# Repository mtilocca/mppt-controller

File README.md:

# MPPT solar charge controller (STM32H743, LM5177 buck-boost)

PV 0-48 V, battery 12-48 V, switched load, DC feed + control port for an external 220 V inverter, Ethernet / isolated CAN / isolated RS485 / USB-C / display.
Design only (not built, not validated). KiCad 10 project generated from code.

PCB editor (routed copper, 195 x 128 mm, 4 layers) and the 3D viewer:

| Doc | Content |
|---|---|
| [docs/00-overview.md](docs/00-overview.md) | What it is, pictures (schematic, PCB, 3D), use cases, comparison with a standard MPPT controller |
| [docs/01-requirements.md](docs/01-requirements.md) | Requirements and assumptions |
| [docs/02-architecture.md](docs/02-architecture.md) | Architecture, part choices, open design items |
| [docs/03-pinmap.md](docs/03-pinmap.md) | STM32 pin allocation (generated) |
| [docs/04-handover.md](docs/04-handover.md) | Current state, what is left, pipeline commands |

Sources: `hardware/mppt_controller.py` (SKiDL generator) -> schematic -> `hardware/place_pcb.py`, routing scripts, `hardware/rebuild.sh`.

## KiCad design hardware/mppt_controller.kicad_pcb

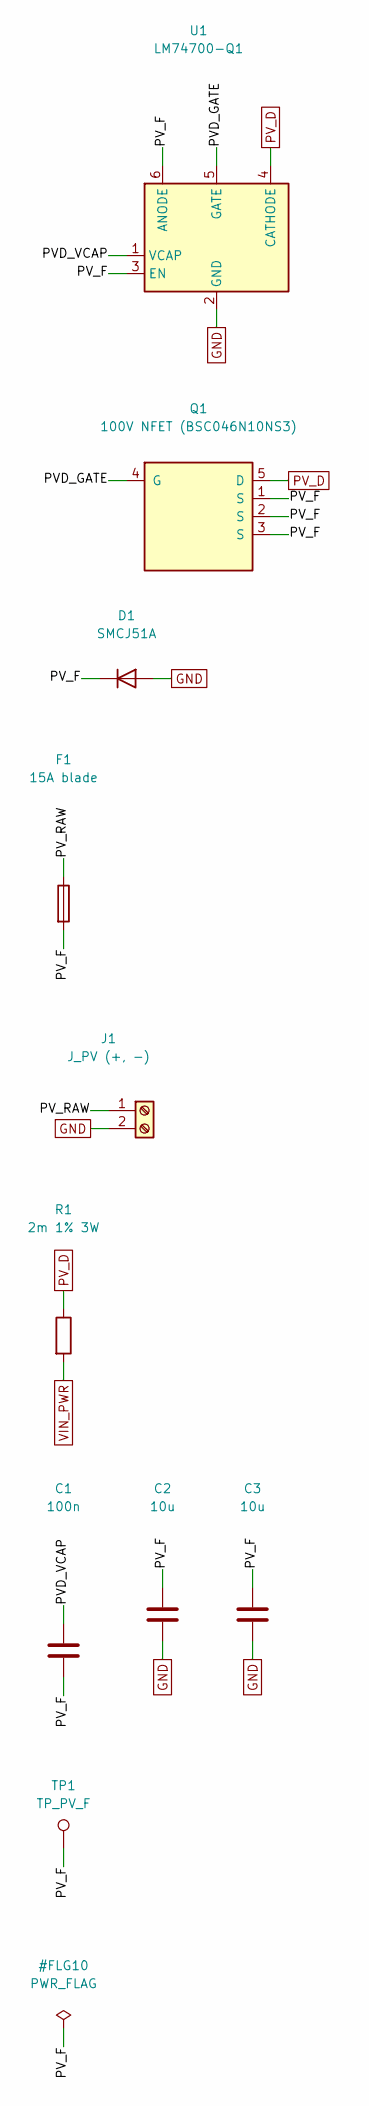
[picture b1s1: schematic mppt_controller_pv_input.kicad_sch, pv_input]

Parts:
C1: 100n; C_0805_2012Metric
C2, C3: 10u; C_1210_3225Metric
D1: SMCJ51A; D_SMC
F1: 15A blade; Fuseholder_Blade_Mini_Keystone_3568
J1: J_PV (+, -); TerminalBlock_Phoenix_MKDS-3-2-5.08_1x02_P5.08mm_Horizontal
Q1: 100V NFET (BSC046N10NS3); TDSON-8-1
R1: 2m 1% 3W; R_2512_6332Metric
TP1: TP_PV_F; TestPoint_Pad_D1.5mm
U1: LM74700-Q1; SOT-23-6

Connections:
/pv_input/PVD_GATE: Q1.4 (G), U1.5 (GATE)
/pv_input/PVD_VCAP: C1.1, U1.1 (VCAP)
/pv_input/PV_F: C1.2, C2.1, C3.1, D1.1 (K), F1.2, Q1.1 (S), Q1.2 (S), Q1.3 (S), TP1.1, U1.3 (EN), U1.6 (ANODE)
/pv_input/PV_RAW: F1.1, J1.1
GND: C2.2, C3.2, D1.2 (A), J1.2, U1.2 (GND); also elsewhere on the board
PV_D: Q1.5 (D), R1.1, U1.4 (CATHODE); also elsewhere on the board
VIN_PWR: R1.2; also elsewhere on the board

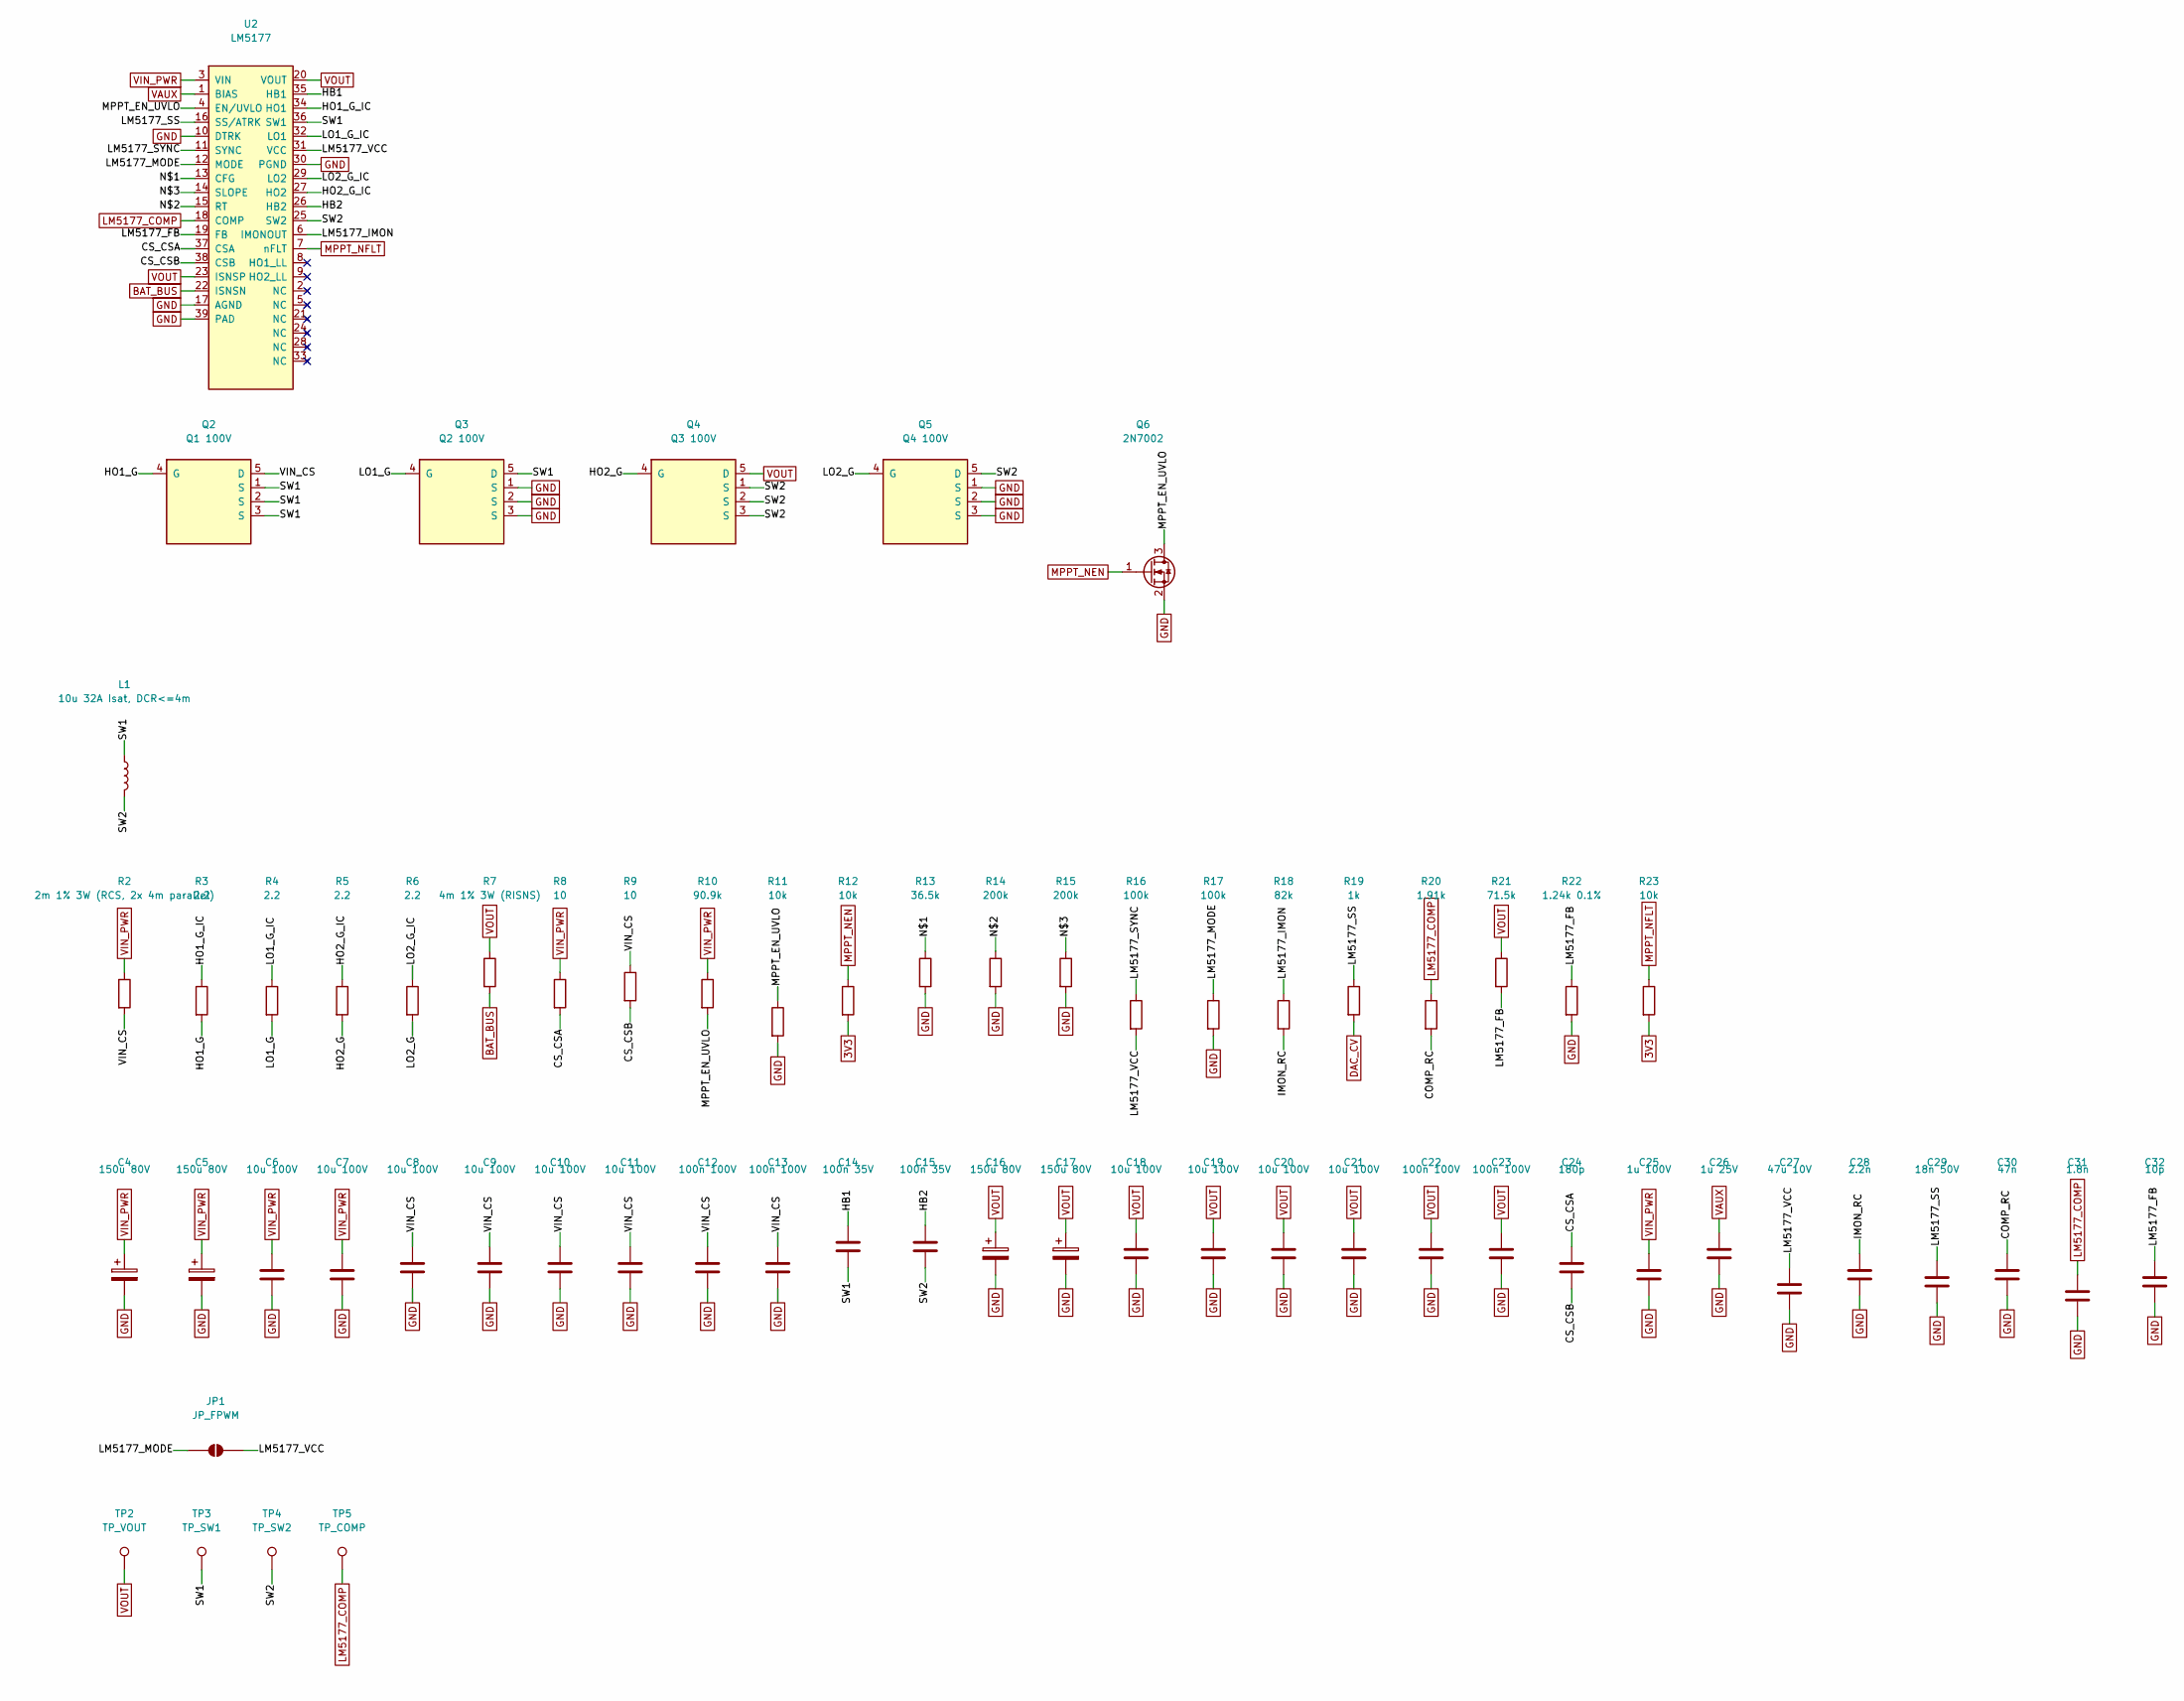
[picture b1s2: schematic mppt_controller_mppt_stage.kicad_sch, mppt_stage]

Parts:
C4, C5, C16, C17: 150u 80V; CP_Elec_10x10.5
C6, C7, C8, C9, C10, C11, C18, C19, C20, C21: 10u 100V; C_1210_3225Metric
C12, C13, C22, C23: 100n 100V; C_0805_2012Metric
C14, C15: 100n 35V; C_0603_1608Metric
C24: 180p; C_0603_1608Metric
C25: 1u 100V; C_0805_2012Metric
C26: 1u 25V; C_0603_1608Metric
C27: 47u 10V; C_1206_3216Metric
C28: 2.2n; C_0603_1608Metric
C29: 18n 50V; C_0603_1608Metric
C30: 47n; C_0603_1608Metric
C31: 1.8n; C_0603_1608Metric
C32: 10p; C_0603_1608Metric
JP1: JP_FPWM; SolderJumper-2_P1.3mm_Open_Pad1.0x1.5mm
L1: 10u 32A Isat, DCR<=4m; L_Toroid_Vertical_L24.6mm_W15.5mm_P11.44mm_Pulse_KM-4
Q2: Q1 100V; TDSON-8-1
Q3: Q2 100V; TDSON-8-1
Q4: Q3 100V; TDSON-8-1
Q5: Q4 100V; TDSON-8-1
Q6: 2N7002; SOT-23
R2: 2m 1% 3W (RCS, 2x 4m parallel); R_2512_6332Metric
R3, R4, R5, R6: 2.2; R_0603_1608Metric
R7: 4m 1% 3W (RISNS); R_2512_6332Metric
R8, R9: 10; R_0603_1608Metric
R10: 90.9k; R_0603_1608Metric
R11, R12, R23: 10k; R_0603_1608Metric
R13: 36.5k; R_0603_1608Metric
R14, R15: 200k; R_0603_1608Metric
R16, R17: 100k; R_0603_1608Metric
R18: 82k; R_0603_1608Metric
R19: 1k; R_0603_1608Metric
R20: 1.91k; R_0603_1608Metric
R21: 71.5k; R_0603_1608Metric
R22: 1.24k 0.1%; R_0603_1608Metric
TP2: TP_VOUT; TestPoint_Pad_D1.5mm
TP3: TP_SW1; TestPoint_Pad_D1.5mm
TP4: TP_SW2; TestPoint_Pad_D1.5mm
TP5: TP_COMP; TestPoint_Pad_D1.5mm
U2: LM5177; HTSSOP-38-1EP_4.4x9.7mm_P0.5mm_EP2.74x4.75mm

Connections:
3V3: R12.2, R23.2; also elsewhere on the board
/mppt_stage/COMP_RC: C30.1, R20.2
/mppt_stage/CS_CSA: C24.1, R8.2, U2.37 (CSA)
/mppt_stage/CS_CSB: C24.2, R9.2, U2.38 (CSB)
/mppt_stage/HB1: C14.1, U2.35 (HB1)
/mppt_stage/HB2: C15.1, U2.26 (HB2)
/mppt_stage/HO1_G: Q2.4 (G), R3.2
/mppt_stage/HO1_G_IC: R3.1, U2.34 (HO1)
/mppt_stage/HO2_G: Q4.4 (G), R5.2
/mppt_stage/HO2_G_IC: R5.1, U2.27 (HO2)
/mppt_stage/IMON_RC: C28.1, R18.2
/mppt_stage/LM5177_FB: C32.1, R21.2, R22.1, U2.19 (FB)
/mppt_stage/LM5177_IMON: R18.1, U2.6 (IMONOUT)
/mppt_stage/LM5177_MODE: JP1.1 (A), R17.1, U2.12 (MODE)
/mppt_stage/LM5177_SS: C29.1, R19.1, U2.16 (SS/ATRK)
/mppt_stage/LM5177_SYNC: R16.1, U2.11 (SYNC)
/mppt_stage/LM5177_VCC: C27.1, JP1.2 (B), R16.2, U2.31 (VCC)
/mppt_stage/LO1_G: Q3.4 (G), R4.2
/mppt_stage/LO1_G_IC: R4.1, U2.32 (LO1)
/mppt_stage/LO2_G: Q5.4 (G), R6.2
/mppt_stage/LO2_G_IC: R6.1, U2.29 (LO2)
/mppt_stage/MPPT_EN_UVLO: Q6.3 (D), R10.2, R11.1, U2.4 (EN/UVLO)
/mppt_stage/N$1: R13.1, U2.13 (CFG)
/mppt_stage/N$2: R14.1, U2.15 (RT)
/mppt_stage/N$3: R15.1, U2.14 (SLOPE)
/mppt_stage/SW1: C14.2, L1.1, Q2.1 (S), Q2.2 (S), Q2.3 (S), Q3.5 (D), TP3.1, U2.36 (SW1)
/mppt_stage/SW2: C15.2, L1.2, Q4.1 (S), Q4.2 (S), Q4.3 (S), Q5.5 (D), TP4.1, U2.25 (SW2)
/mppt_stage/VIN_CS: C8.1, C9.1, C10.1, C11.1, C12.1, C13.1, Q2.5 (D), R2.2, R9.1
BAT_BUS: R7.2, U2.22 (ISNSN); also elsewhere on the board
DAC_CV: R19.2; also elsewhere on the board
GND: C4.2, C5.2, C6.2, C7.2, C8.2, C9.2, C10.2, C11.2, C12.2, C13.2, C16.2, C17.2, C18.2, C19.2, C20.2, C21.2, C22.2, C23.2, C25.2, C26.2, C27.2, C28.2, C29.2, C30.2, C31.2, C32.2, Q3.1 (S), Q3.2 (S), Q3.3 (S), Q5.1 (S), Q5.2 (S), Q5.3 (S), Q6.2 (S), R11.2, R13.2, R14.2, R15.2, R17.2, R22.2, U2.10 (DTRK), U2.17 (AGND), U2.30 (PGND), U2.39 (PAD); also elsewhere on the board
LM5177_COMP: C31.1, R20.1, TP5.1, U2.18 (COMP); also elsewhere on the board
MPPT_NEN: Q6.1 (G), R12.1; also elsewhere on the board
MPPT_NFLT: R23.1, U2.7 (nFLT); also elsewhere on the board
VAUX: C26.1, U2.1 (BIAS); also elsewhere on the board
VIN_PWR: C4.1, C5.1, C6.1, C7.1, C25.1, R2.1, R8.1, R10.1, U2.3 (VIN); also elsewhere on the board
VOUT: C16.1, C17.1, C18.1, C19.1, C20.1, C21.1, C22.1, C23.1, Q4.5 (D), R7.1, R21.1, TP2.1, U2.20 (VOUT), U2.23 (ISNSP); also elsewhere on the board

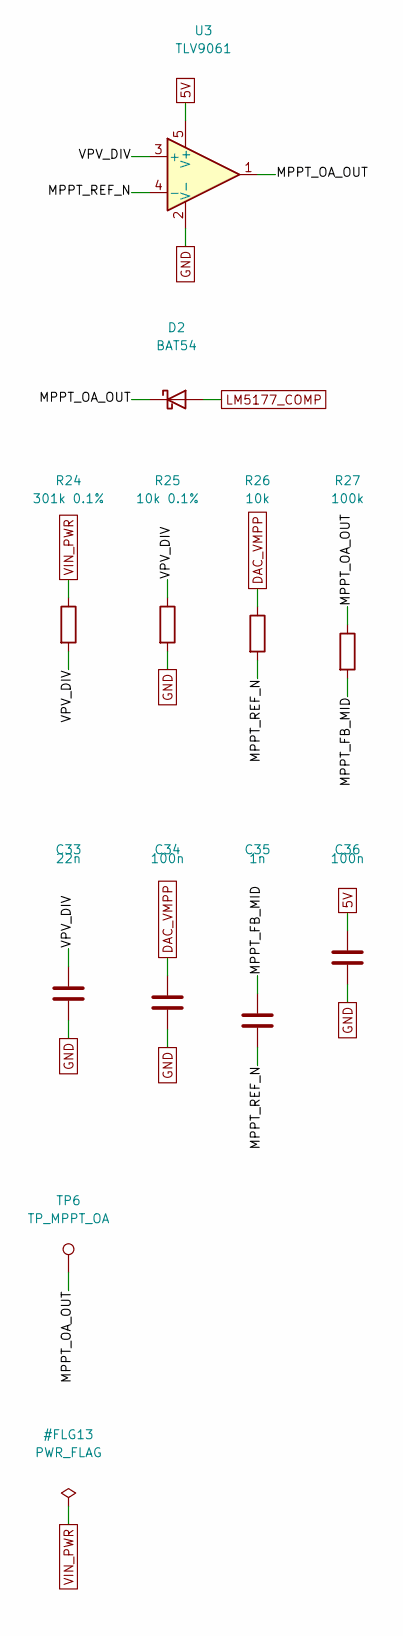
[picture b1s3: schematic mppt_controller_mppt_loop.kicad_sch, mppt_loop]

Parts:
C33: 22n; C_0603_1608Metric
C34, C36: 100n; C_0603_1608Metric
C35: 1n; C_0603_1608Metric
D2: BAT54; D_SOD-123
R24: 301k 0.1%; R_0603_1608Metric
R25: 10k 0.1%; R_0603_1608Metric
R26: 10k; R_0603_1608Metric
R27: 100k; R_0603_1608Metric
TP6: TP_MPPT_OA; TestPoint_Pad_D1.5mm
U3: TLV9061; SOT-23-5

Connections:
5V: C36.1, U3.5 (V+); also elsewhere on the board
/mppt_loop/MPPT_FB_MID: C35.1, R27.2
/mppt_loop/MPPT_OA_OUT: D2.1 (K), R27.1, TP6.1, U3.1
/mppt_loop/MPPT_REF_N: C35.2, R26.2, U3.4 (-)
/mppt_loop/VPV_DIV: C33.1, R24.2, R25.1, U3.3 (+)
DAC_VMPP: C34.1, R26.1; also elsewhere on the board
GND: C33.2, C34.2, C36.2, R25.2, U3.2 (V-); also elsewhere on the board
LM5177_COMP: D2.2 (A); also elsewhere on the board
VIN_PWR: R24.1; also elsewhere on the board

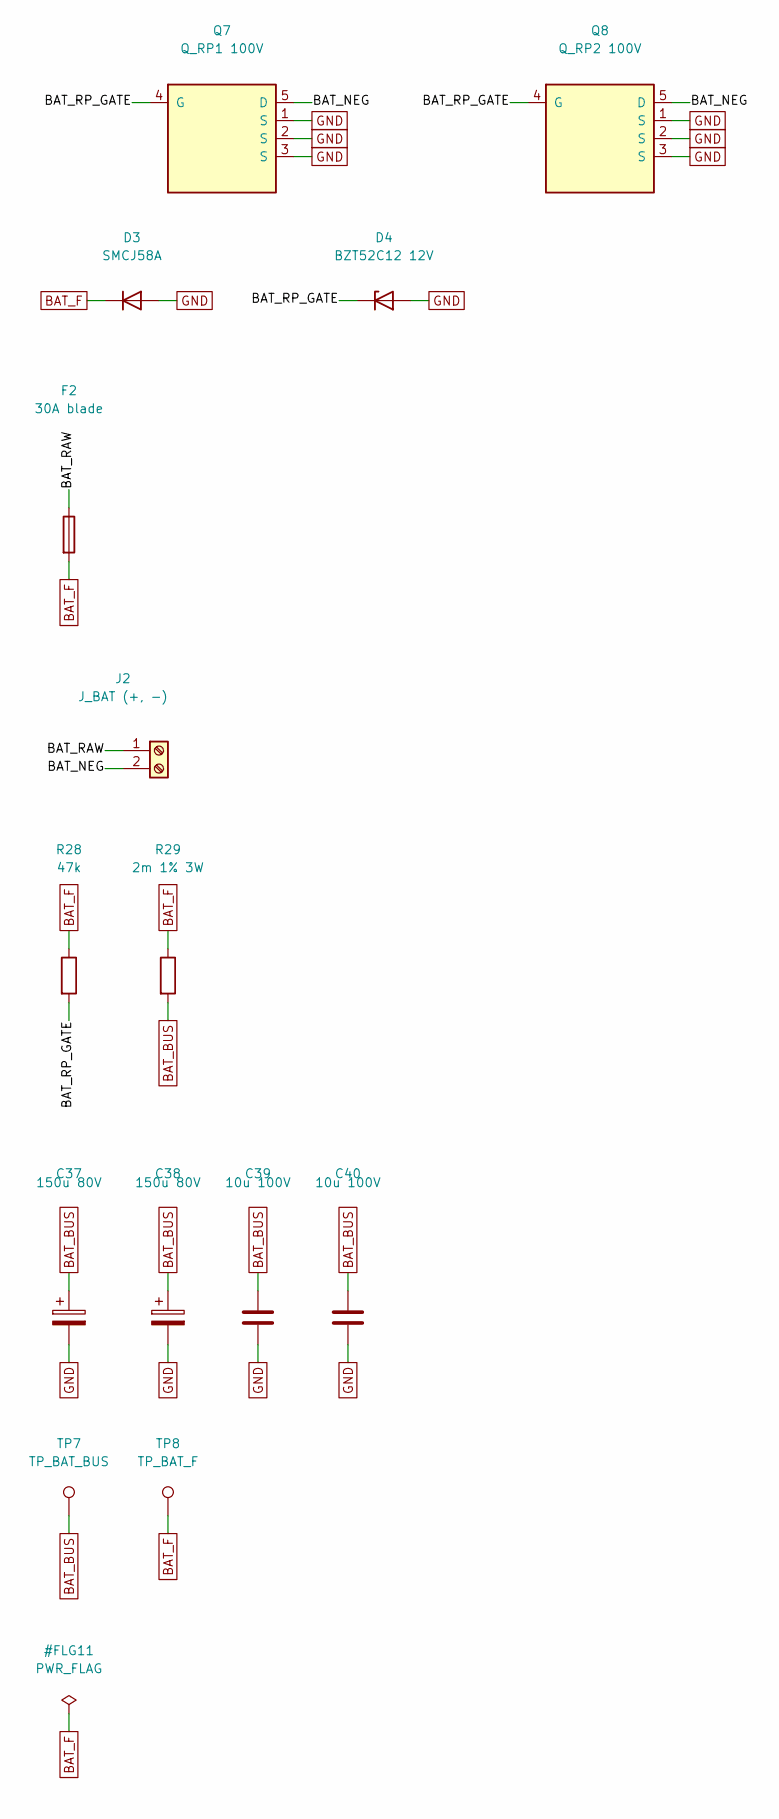
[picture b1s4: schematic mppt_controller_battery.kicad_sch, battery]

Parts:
C37, C38: 150u 80V; CP_Elec_10x10.5
C39, C40: 10u 100V; C_1210_3225Metric
D3: SMCJ58A; D_SMC
D4: BZT52C12 12V; D_SOD-123
F2: 30A blade; Fuseholder_Blade_ATO_Littelfuse_Pudenz_2_Pin
J2: J_BAT (+, -); TerminalBlock_Phoenix_MKDS-3-2-5.08_1x02_P5.08mm_Horizontal
Q7: Q_RP1 100V; TDSON-8-1
Q8: Q_RP2 100V; TDSON-8-1
R28: 47k; R_1206_3216Metric
R29: 2m 1% 3W; R_2512_6332Metric
TP7: TP_BAT_BUS; TestPoint_Pad_D1.5mm
TP8: TP_BAT_F; TestPoint_Pad_D1.5mm

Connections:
/battery/BAT_NEG: J2.2, Q7.5 (D), Q8.5 (D)
/battery/BAT_RAW: F2.1, J2.1
/battery/BAT_RP_GATE: D4.1 (K), Q7.4 (G), Q8.4 (G), R28.2
BAT_BUS: C37.1, C38.1, C39.1, C40.1, R29.2, TP7.1; also elsewhere on the board
BAT_F: D3.1 (K), F2.2, R28.1, R29.1, TP8.1; also elsewhere on the board
GND: C37.2, C38.2, C39.2, C40.2, D3.2 (A), D4.2 (A), Q7.1 (S), Q7.2 (S), Q7.3 (S), Q8.1 (S), Q8.2 (S), Q8.3 (S); also elsewhere on the board

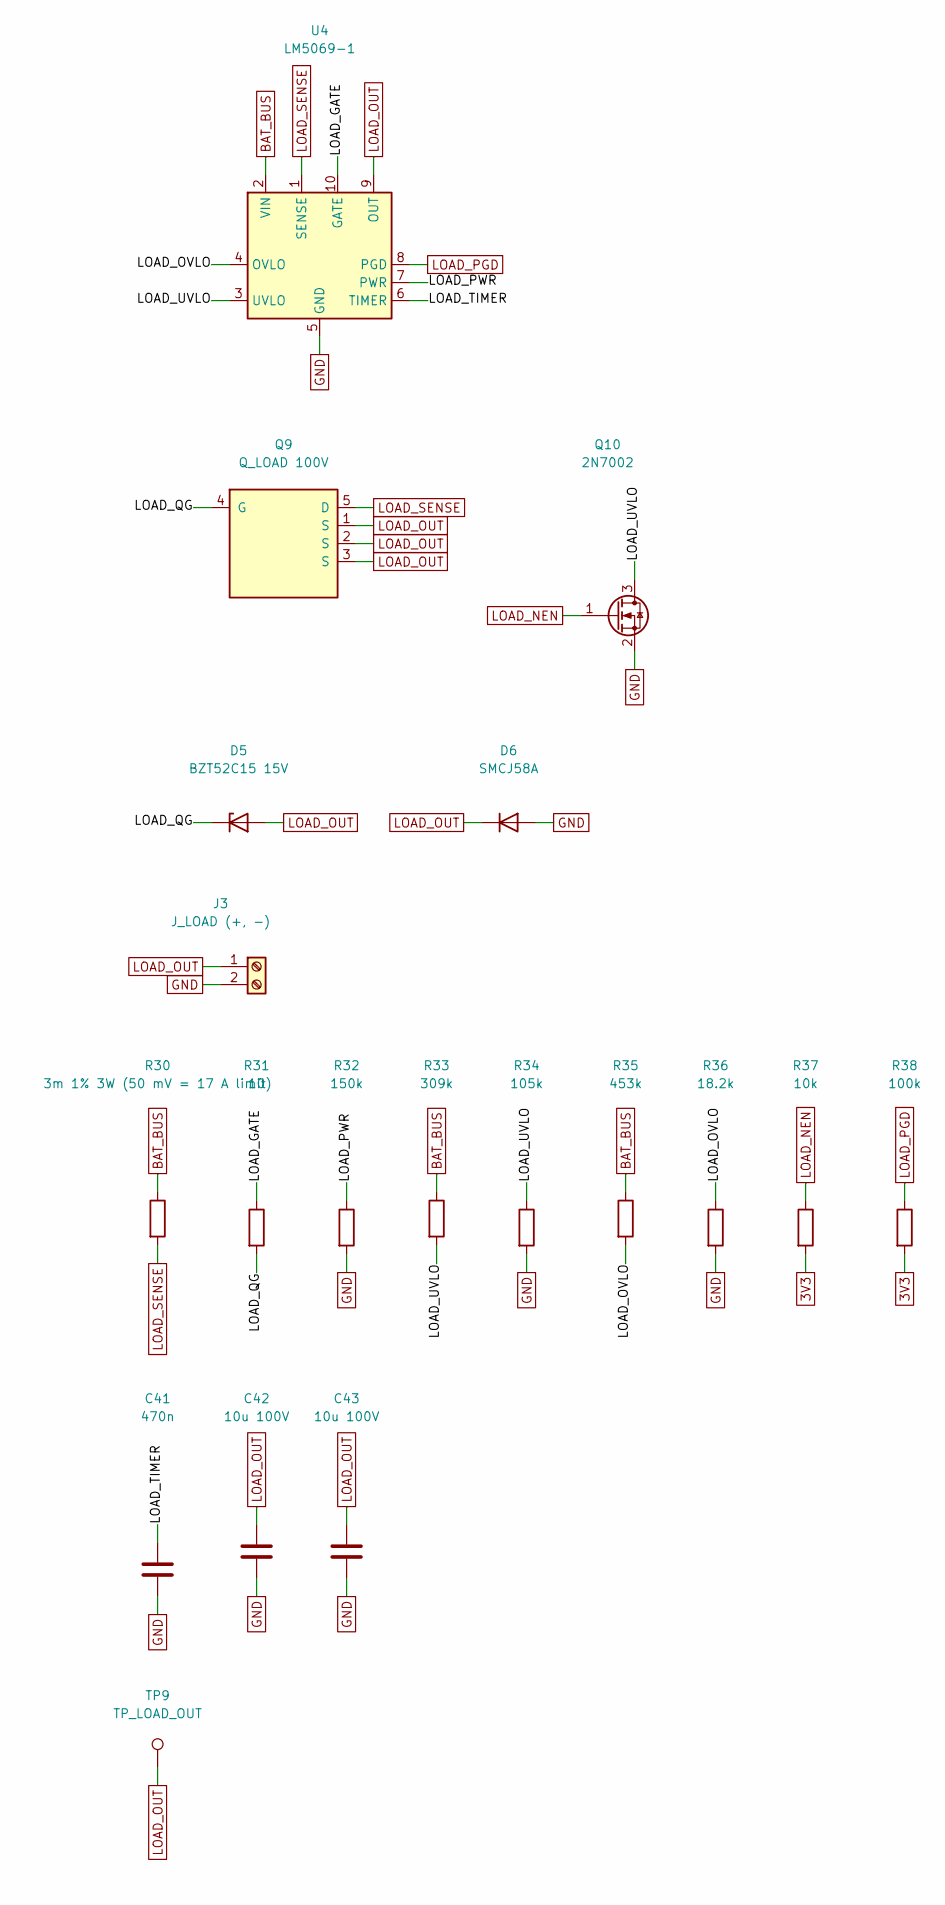
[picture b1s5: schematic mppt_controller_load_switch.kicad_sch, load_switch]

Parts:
C41: 470n; C_0603_1608Metric
C42, C43: 10u 100V; C_1210_3225Metric
D5: BZT52C15 15V; D_SOD-123
D6: SMCJ58A; D_SMC
J3: J_LOAD (+, -); TerminalBlock_Phoenix_MKDS-3-2-5.08_1x02_P5.08mm_Horizontal
Q9: Q_LOAD 100V; TDSON-8-1
Q10: 2N7002; SOT-23
R30: 3m 1% 3W (50 mV = 17 A limit); R_2512_6332Metric
R31: 10; R_0603_1608Metric
R32: 150k; R_0603_1608Metric
R33: 309k; R_0603_1608Metric
R34: 105k; R_0603_1608Metric
R35: 453k; R_0603_1608Metric
R36: 18.2k; R_0603_1608Metric
R37: 10k; R_0603_1608Metric
R38: 100k; R_0603_1608Metric
TP9: TP_LOAD_OUT; TestPoint_Pad_D1.5mm
U4: LM5069-1; MSOP-10_3x3mm_P0.5mm

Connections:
3V3: R37.2, R38.2; also elsewhere on the board
/load_switch/LOAD_GATE: R31.1, U4.10 (GATE)
/load_switch/LOAD_OVLO: R35.2, R36.1, U4.4 (OVLO)
/load_switch/LOAD_PWR: R32.1, U4.7 (PWR)
/load_switch/LOAD_QG: D5.1 (K), Q9.4 (G), R31.2
/load_switch/LOAD_TIMER: C41.1, U4.6 (TIMER)
/load_switch/LOAD_UVLO: Q10.3 (D), R33.2, R34.1, U4.3 (UVLO)
BAT_BUS: R30.1, R33.1, R35.1, U4.2 (VIN); also elsewhere on the board
GND: C41.2, C42.2, C43.2, D6.2 (A), J3.2, Q10.2 (S), R32.2, R34.2, R36.2, U4.5 (GND); also elsewhere on the board
LOAD_NEN: Q10.1 (G), R37.1; also elsewhere on the board
LOAD_OUT: C42.1, C43.1, D5.2 (A), D6.1 (K), J3.1, Q9.1 (S), Q9.2 (S), Q9.3 (S), TP9.1, U4.9 (OUT); also elsewhere on the board
LOAD_PGD: R38.1, U4.8 (PGD); also elsewhere on the board
LOAD_SENSE: Q9.5 (D), R30.2, U4.1 (SENSE); also elsewhere on the board

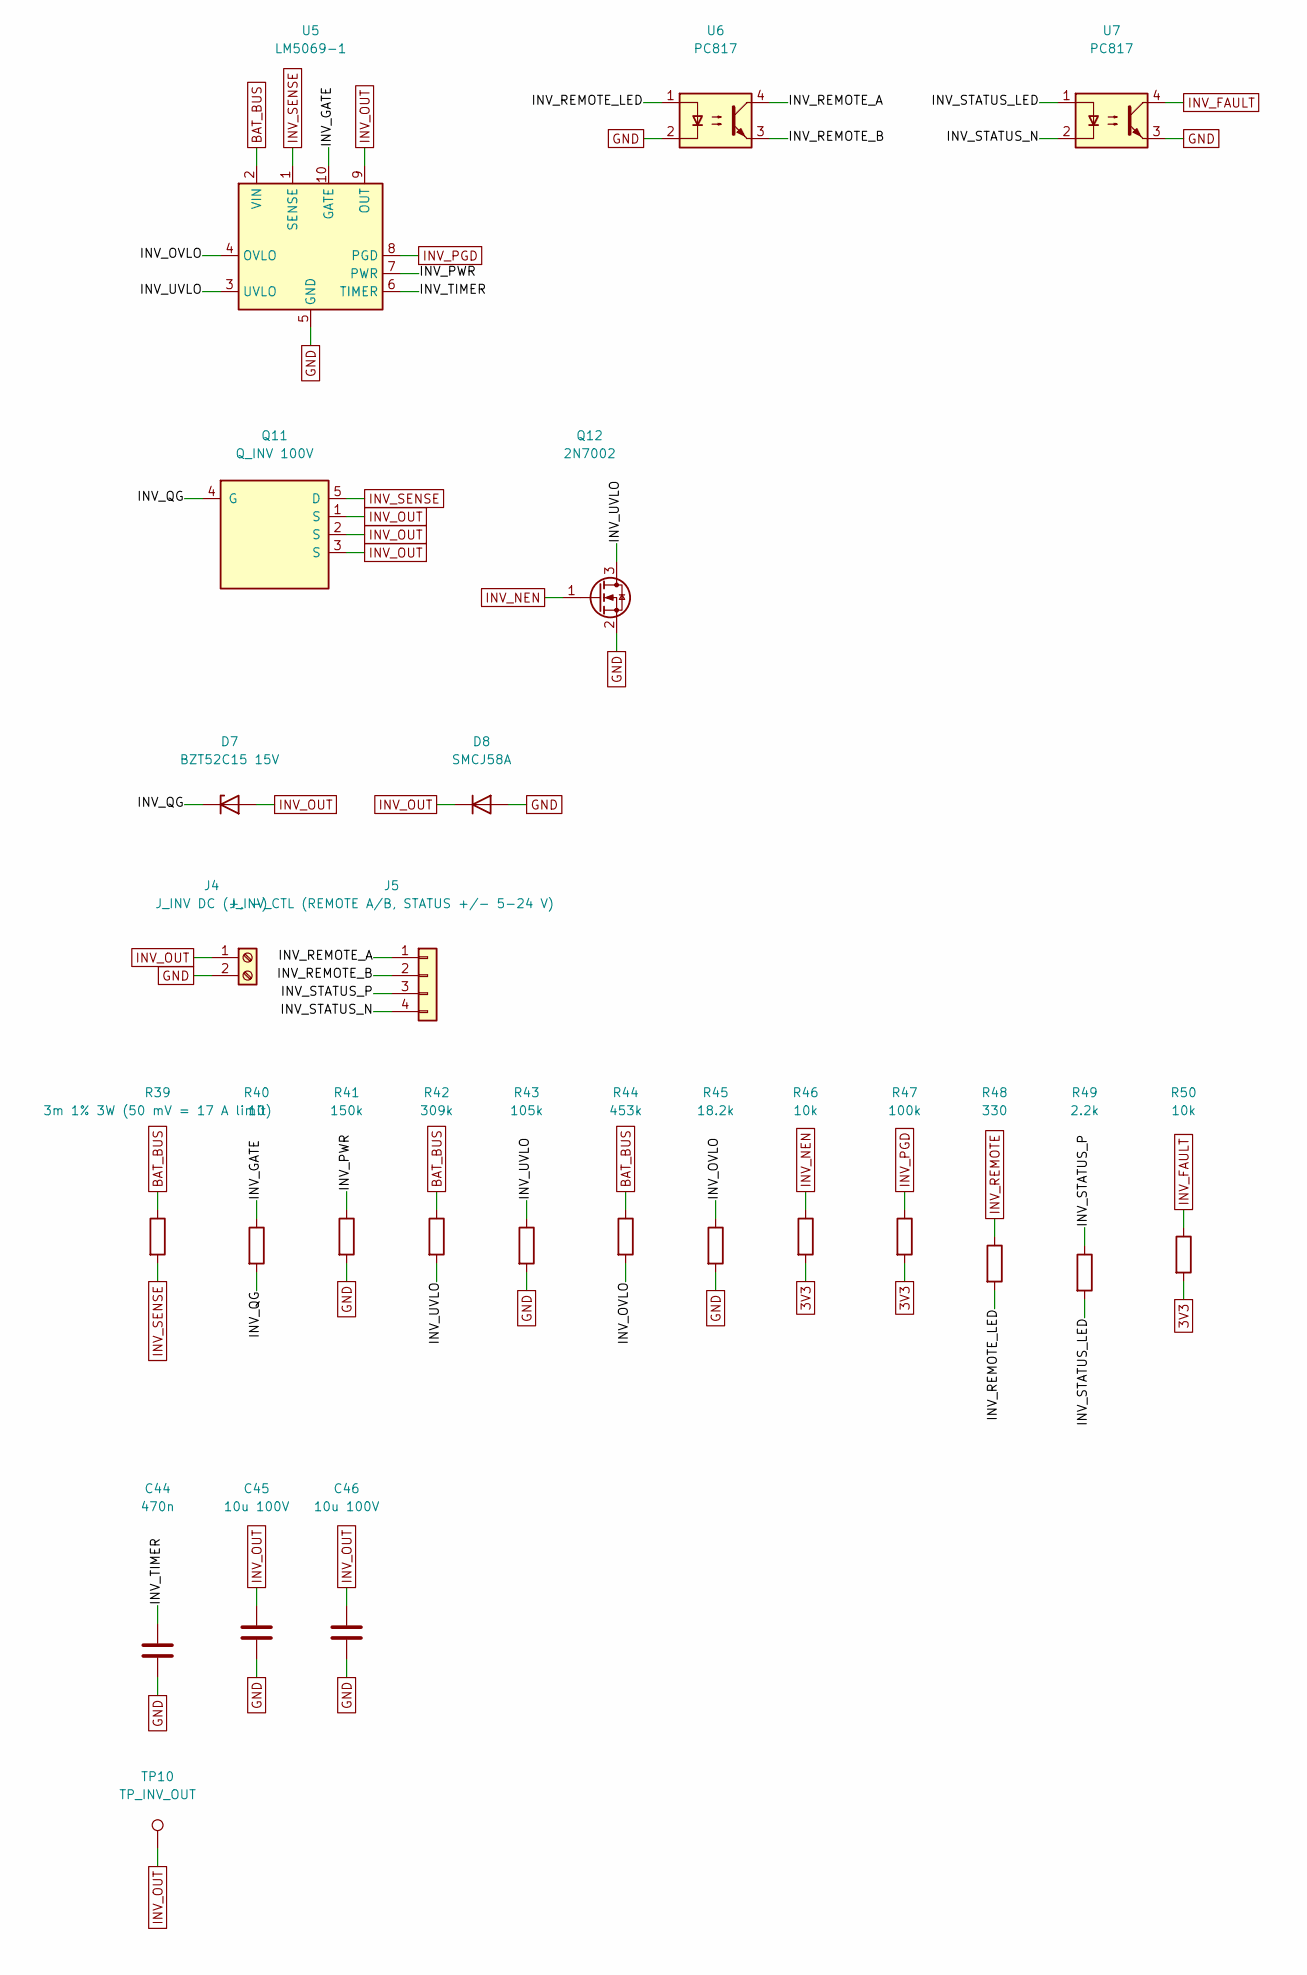
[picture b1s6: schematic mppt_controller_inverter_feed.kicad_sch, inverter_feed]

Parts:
C44: 470n; C_0603_1608Metric
C45, C46: 10u 100V; C_1210_3225Metric
D7: BZT52C15 15V; D_SOD-123
D8: SMCJ58A; D_SMC
J4: J_INV DC (+, -); TerminalBlock_Phoenix_MKDS-3-2-5.08_1x02_P5.08mm_Horizontal
J5: J_INV_CTL (REMOTE A/B, STATUS +/- 5-24 V); TerminalBlock_Phoenix_PT-1,5-4-3.5-H_1x04_P3.50mm_Horizontal
Q11: Q_INV 100V; TDSON-8-1
Q12: 2N7002; SOT-23
R39: 3m 1% 3W (50 mV = 17 A limit); R_2512_6332Metric
R40: 10; R_0603_1608Metric
R41: 150k; R_0603_1608Metric
R42: 309k; R_0603_1608Metric
R43: 105k; R_0603_1608Metric
R44: 453k; R_0603_1608Metric
R45: 18.2k; R_0603_1608Metric
R46, R50: 10k; R_0603_1608Metric
R47: 100k; R_0603_1608Metric
R48: 330; R_0603_1608Metric
R49: 2.2k; R_0603_1608Metric
TP10: TP_INV_OUT; TestPoint_Pad_D1.5mm
U5: LM5069-1; MSOP-10_3x3mm_P0.5mm
U6, U7: PC817; SMDIP-4_W9.53mm

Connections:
3V3: R46.2, R47.2, R50.2; also elsewhere on the board
/inverter_feed/INV_GATE: R40.1, U5.10 (GATE)
/inverter_feed/INV_OVLO: R44.2, R45.1, U5.4 (OVLO)
/inverter_feed/INV_PWR: R41.1, U5.7 (PWR)
/inverter_feed/INV_QG: D7.1 (K), Q11.4 (G), R40.2
/inverter_feed/INV_REMOTE_A: J5.1, U6.4
/inverter_feed/INV_REMOTE_B: J5.2, U6.3
/inverter_feed/INV_REMOTE_LED: R48.2, U6.1
/inverter_feed/INV_STATUS_LED: R49.2, U7.1
/inverter_feed/INV_STATUS_N: J5.4, U7.2
/inverter_feed/INV_STATUS_P: J5.3, R49.1
/inverter_feed/INV_TIMER: C44.1, U5.6 (TIMER)
/inverter_feed/INV_UVLO: Q12.3 (D), R42.2, R43.1, U5.3 (UVLO)
BAT_BUS: R39.1, R42.1, R44.1, U5.2 (VIN); also elsewhere on the board
GND: C44.2, C45.2, C46.2, D8.2 (A), J4.2, Q12.2 (S), R41.2, R43.2, R45.2, U5.5 (GND), U6.2, U7.3; also elsewhere on the board
INV_FAULT: R50.1, U7.4; also elsewhere on the board
INV_NEN: Q12.1 (G), R46.1; also elsewhere on the board
INV_OUT: C45.1, C46.1, D7.2 (A), D8.1 (K), J4.1, Q11.1 (S), Q11.2 (S), Q11.3 (S), TP10.1, U5.9 (OUT); also elsewhere on the board
INV_PGD: R47.1, U5.8 (PGD); also elsewhere on the board
INV_REMOTE: R48.1; also elsewhere on the board
INV_SENSE: Q11.5 (D), R39.2, U5.1 (SENSE); also elsewhere on the board
